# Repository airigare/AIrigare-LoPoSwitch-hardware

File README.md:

LoPoSwitch is designed to switch 12V devices on and off. It can be ruled by Smartphone or Cloud. LoPoSwitch connects to Cloud or Smartphone over WiFi or Bluetooth LE.

## Changelog

### v.0.9.1
- New WiFi Module Adafruit ATWINC1500 WiFi Breakout

### v.0.7
- Connect Digital Pin 1 (Pin3) to Reset Pin. This makes Software Reset possible

### v.0.6
- Switch WiFi Module with Relais
- Redesign PCB Board
- Add 47nP Capacitor

### v.0.5
- Switch WiFi module with Mosfet Transistor            
How to use：

At editor, Click the document icon on the topbar, via "Document" > "Open" > "EasyEDA Source", and select json file, then open it at the editor.

如何使用：

在编辑器顶部工具栏，点击“文档”图标，选择 “文档” > “打开” > “EasyEDA源码”，选择json文件打开即可。

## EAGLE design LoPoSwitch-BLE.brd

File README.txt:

LoPoSwitch is designed to switch 12V devices on and off. It can be ruled by Smartphone or Cloud. LoPoSwitch connects to Cloud or Smartphone over WiFi or Bluetooth LE.

## Changelog
### v.0.6
- Switch WiFi Module with Relais
- Redesign PCB Board
- Add 47nP Capacitor

### v.0.5
- Switch WiFi module with Mosfet Transistor            
How to use：

At editor, Click the document icon on the topbar, via "Document" > "Open" > "EasyEDA Source", and select json file, then open it at the editor.

如何使用：

在编辑器顶部工具栏，点击“文档”图标，选择 “文档” > “打开” > “EasyEDA源码”，选择json文件打开即可。

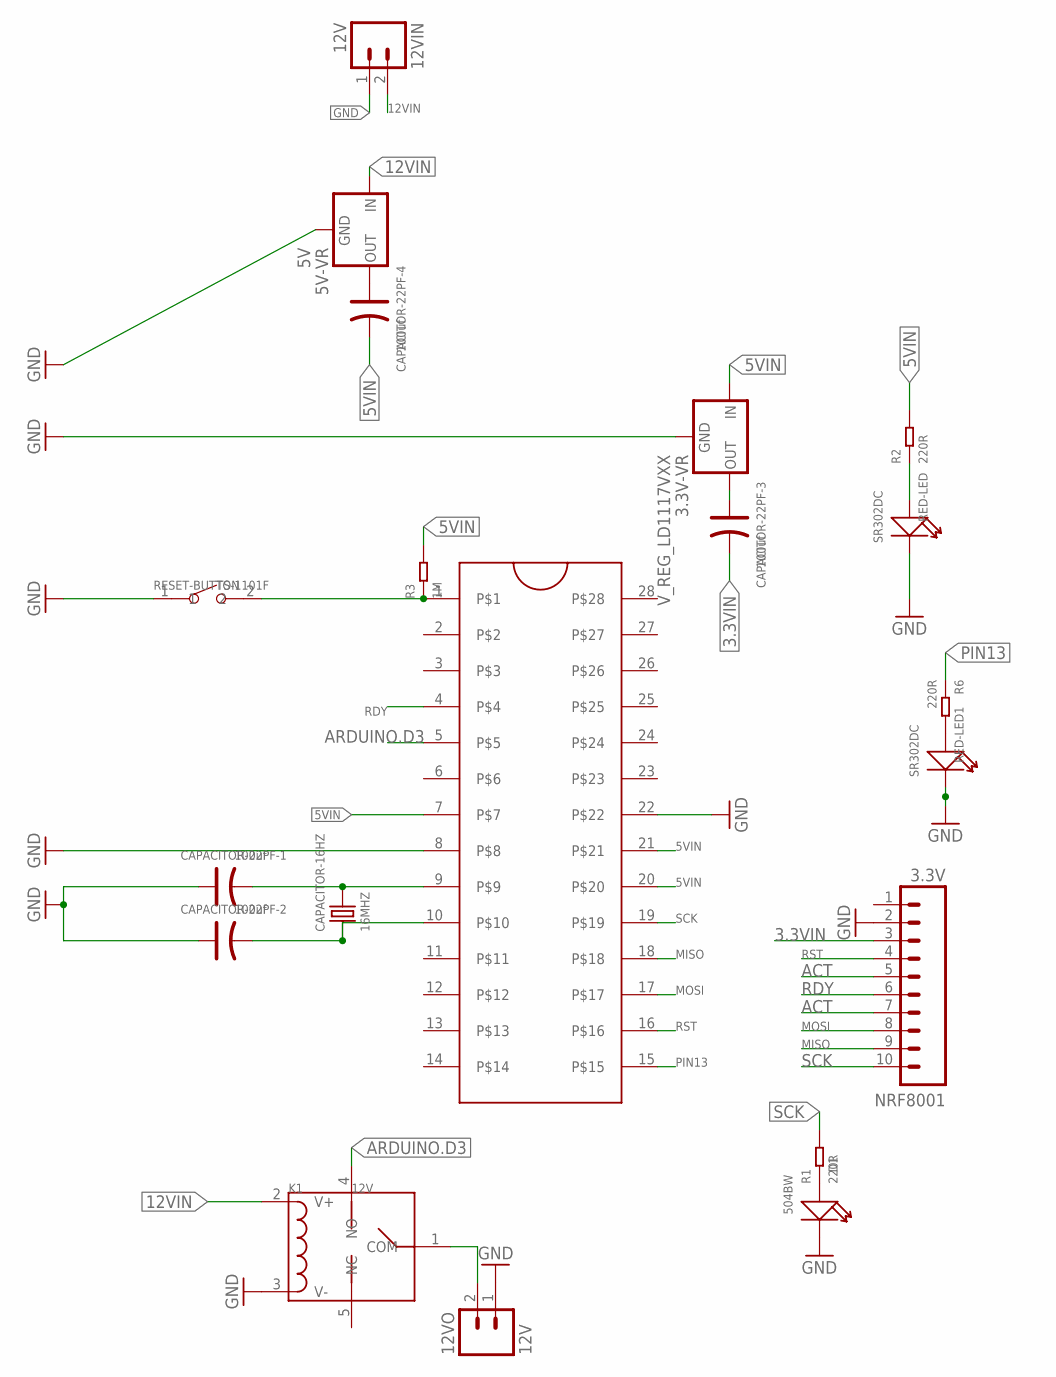
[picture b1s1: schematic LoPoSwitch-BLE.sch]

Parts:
3.3V-VR: V_REG_LD1117VXX; 78XXL
5V-VR: 5V; TO-220-ALT
12VIN, 12VO: 12V; JST-2-PTH
ATMEGA328: ZIFSOCKET-28-3ZIFFSOCKET-28-3; DIL28-3-ZIF_SOCKET
CAPACITOR-16HZ: 16MHZ; HC49US
CAPACITOR-22PF-1, CAPACITOR-22PF-2, CAPACITOR-22PF-3, CAPACITOR-22PF-4: 100uf; PC-D5.3MM
D1: 504BW; LED2-2.54-D5.0MM
K1: 12V; REY5-19.0X15.0X15.0MM
NRF8001: 3.3V; 1X10
R1, R2, R6: 220R; PR-D2.3XL6.5MM
R3: 1M; PR-D2.3XL6.5MM
RED-LED, RED-LED1: SR302DC; LED2-2.54-D3.0MM
RESET-BUTTON: TS-1101F; SW2-5.0-6.0X3.0X4.3MM

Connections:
3.3VIN: CAPACITOR-22PF-3.-, NRF8001.3
5VIN: 3.3V-VR.OUT (IN), ATMEGA328.7, ATMEGA328.20, ATMEGA328.21, CAPACITOR-22PF-4.-, R2.2, R3.2
12VIN: 5V-VR.IN, 12VIN.2, K1.2 (V+)
ACT: NRF8001.5, NRF8001.7
ARDUINO.D3: ATMEGA328.5, K1.4 (NO)
GND: 3.3V-VR.IN (GND), 5V-VR.GND, 12VIN.1, 12VO.1, ATMEGA328.8, ATMEGA328.22, CAPACITOR-22PF-1.+, CAPACITOR-22PF-2.+, D1.-, K1.3 (V-), NRF8001.2, RED-LED.K (-), RED-LED1.K (-), RESET-BUTTON.1
MISO: ATMEGA328.18, NRF8001.9
MOSI: ATMEGA328.17, NRF8001.8
unnamed: 12VO.2, K1.1 (COM)
unnamed: R6.2, RED-LED1.A (+)
unnamed: ATMEGA328.1, R3.1, RESET-BUTTON.2
unnamed: 3.3V-VR.GND (OUT), CAPACITOR-22PF-3.+
unnamed: 5V-VR.OUT, CAPACITOR-22PF-4.+
unnamed: D1.+, R1.1
unnamed: R2.1, RED-LED.A (+)
unnamed: ATMEGA328.9, CAPACITOR-16HZ.2, CAPACITOR-22PF-1.-
unnamed: ATMEGA328.10, CAPACITOR-16HZ.1, CAPACITOR-22PF-2.-
PIN13: ATMEGA328.15, R6.1
RDY: ATMEGA328.4, NRF8001.6
RST: ATMEGA328.16, NRF8001.4
SCK: ATMEGA328.19, NRF8001.10, R1.2

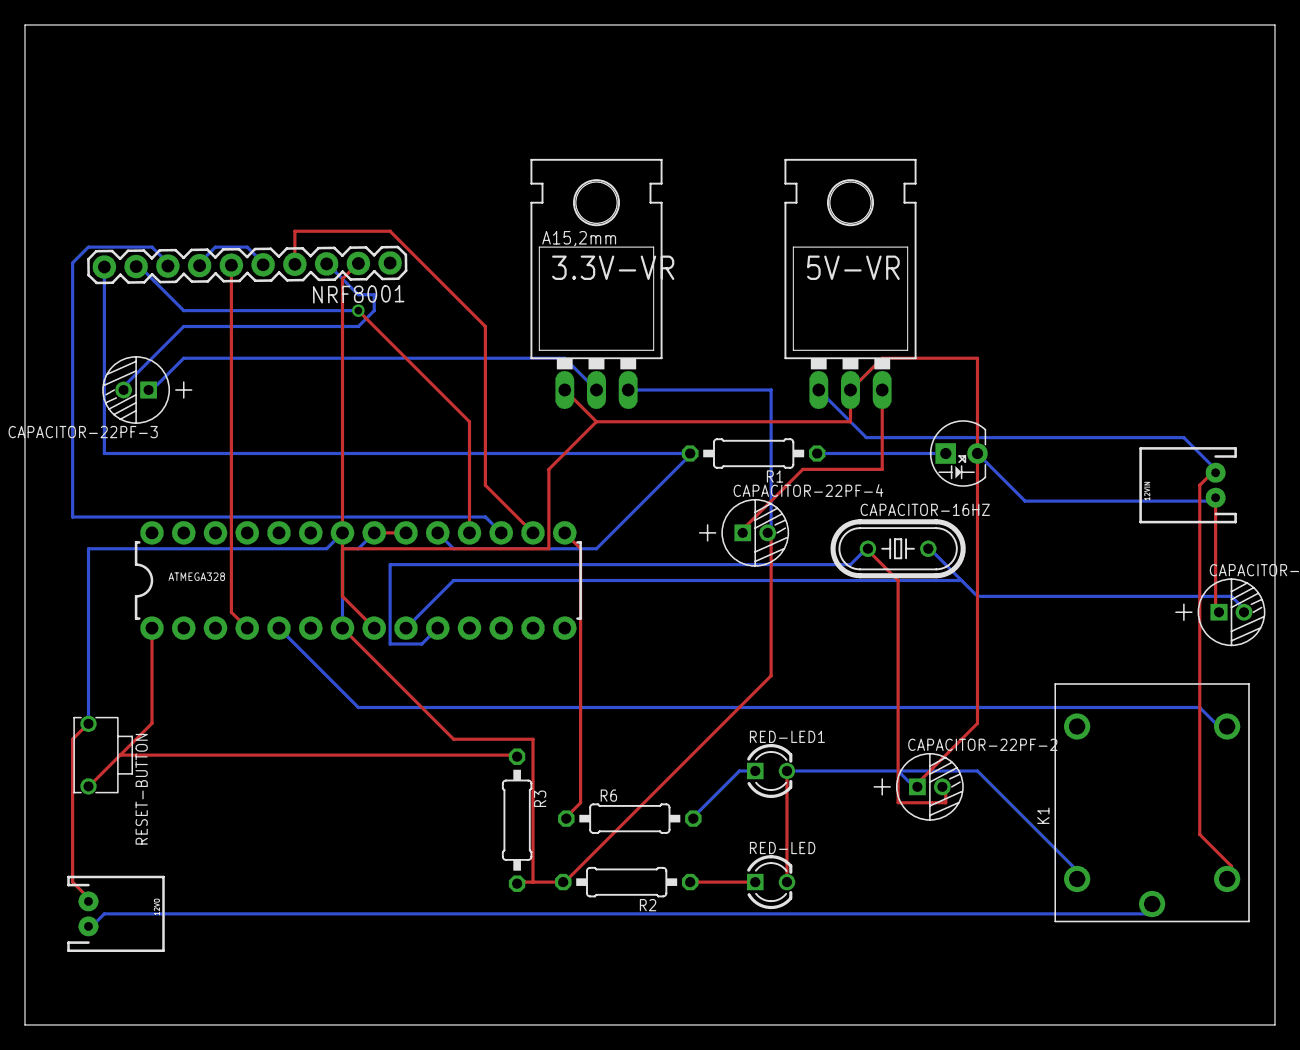
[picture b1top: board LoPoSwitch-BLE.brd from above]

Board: 2 copper layers, 100.0 x 80.0 mm, 20 parts (0 on the bottom side), 21 nets.

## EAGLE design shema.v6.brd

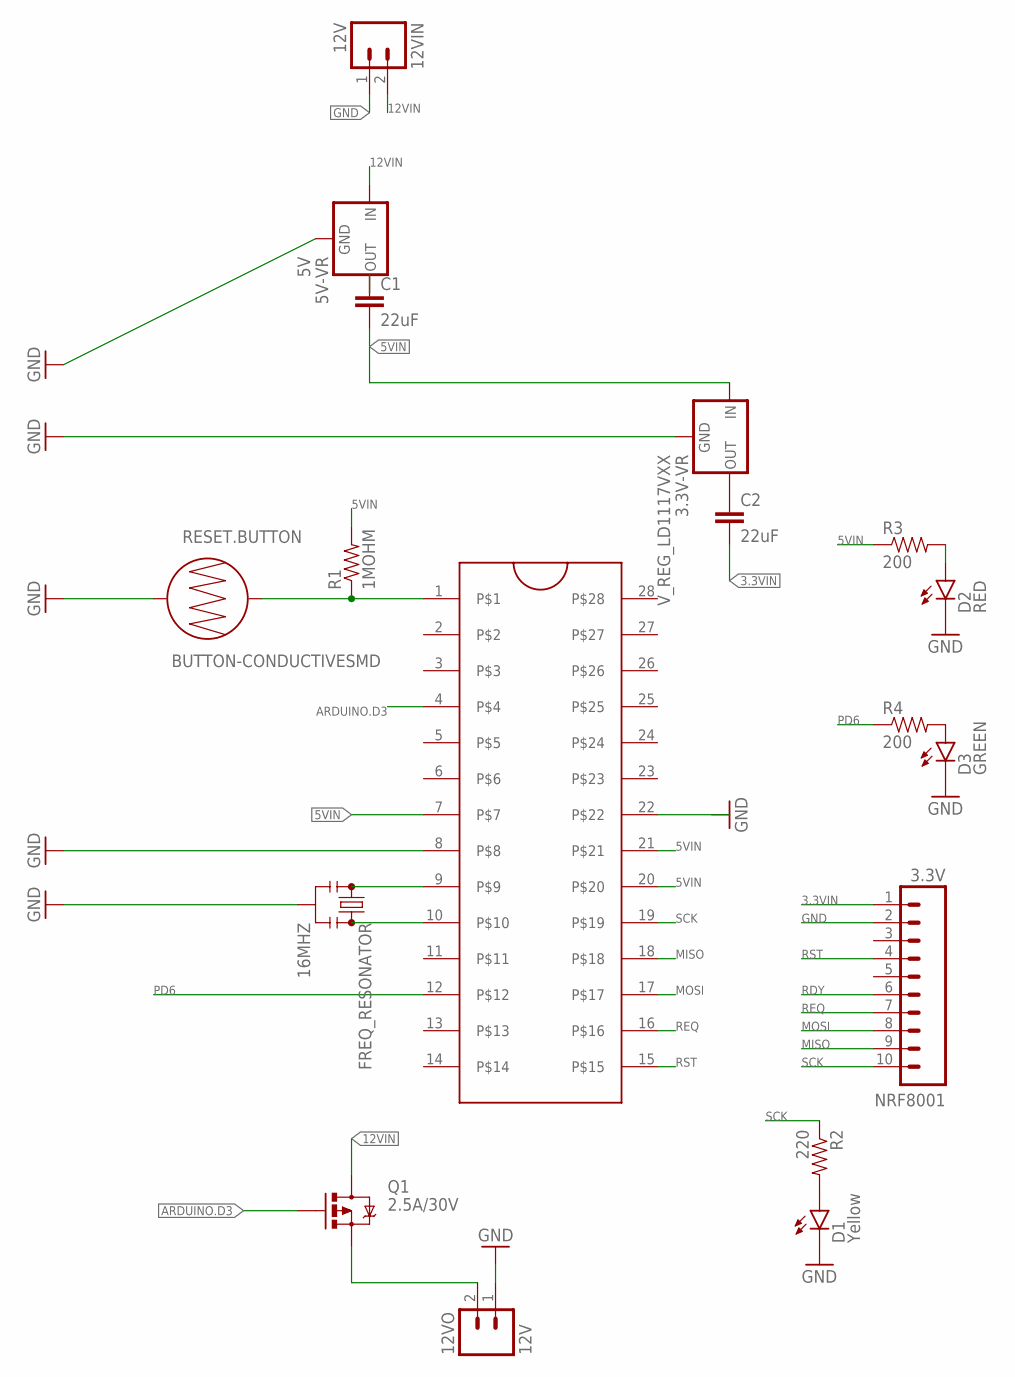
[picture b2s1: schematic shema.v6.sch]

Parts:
3.3V-VR: V_REG_LD1117VXX; 78XXL
5V-VR: 5V; TO-220-ALT
12VIN, 12VO: 12V; JST-2-PTH
ATMEGA328: ZIFSOCKET-28-3ZIFFSOCKET-28-3; DIL28-3-ZIF_SOCKET
C1, C2: 22uF; 1210
D1: Yellow; LED-0603
D2: RED; LED-0603
D3: GREEN; LED-1206
FREQ_RESONATOR: 16MHZ; RESONATOR-SMD
NRF8001: 3.3V; 1X10
Q1: 2.5A/30V; SOT23-3
R1: 1MOHM; 1/6W-RES
R2: 220; AXIAL-0.3EZ
R3, R4: 200; 0603-RES
RESET.BUTTON: BUTTON-CONDUCTIVESMD; BUTTON-CONDUCTIVE

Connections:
3.3VIN: C2.2, NRF8001.1
5VIN: 3.3V-VR.OUT (IN), ATMEGA328.7, ATMEGA328.20, ATMEGA328.21, C1.2, R1.2, R3.1
12VIN: 5V-VR.IN, 12VIN.2, Q1.3 (D)
ARDUINO.D3: ATMEGA328.4, Q1.1 (G)
GND: 3.3V-VR.IN (GND), 5V-VR.GND, 12VIN.1, 12VO.1, ATMEGA328.8, D1.C, D2.C, D3.C, FREQ_RESONATOR.2, NRF8001.2, RESET.BUTTON.1
MISO: ATMEGA328.18, NRF8001.9
MOSI: ATMEGA328.17, NRF8001.8
unnamed: ATMEGA328.9, FREQ_RESONATOR.1
unnamed: ATMEGA328.10, FREQ_RESONATOR.3
unnamed: ATMEGA328.1, R1.1, RESET.BUTTON.2
unnamed: 12VO.2, Q1.2 (S)
unnamed: 5V-VR.OUT, C1.1
unnamed: 3.3V-VR.GND (OUT), C2.1
unnamed: D1.A, R2.P$2 (2)
unnamed: D2.A, R3.2
unnamed: D3.A, R4.2
PD6: ATMEGA328.12, R4.1
RDY: NRF8001.6
REQ: ATMEGA328.16, NRF8001.7
RST: ATMEGA328.15, NRF8001.4
SCK: ATMEGA328.19, NRF8001.10, R2.P$1 (1)

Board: 2 copper layers, 18 parts (0 on the bottom side), 20 nets, no tracks yet.

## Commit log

2016-08-18 Replace MOSFET
2017-09-27 Restyle Board with SeedStudio Elements
2017-09-28 Change Grid to 0.05 inch
2017-09-28 Generate Seed Gerber File
2018-11-16 some versione
2018-11-16 Version 2
2018-11-16 Submit Version 2
2018-11-16 Replace CMD by TO
2018-11-17 V2.1
2019-03-20 v.0.5
    Changelog v.0.5
    - Switch WiFi module with Mosfet Transistor
2019-03-20 v.0.6
    ### v.0.6
    - Switch WiFi Module with Relais
    - Redesign PCB Board
    - Add 47nP Capacitor
2019-03-20 Switch to MarkDown
    Switch Project Description to MarkDown Format
2019-03-21 v.0.7
    Connect Digital Pin to Reset Pin to do Software Reset
2019-05-03 v.0.9.1
    v.0.9.1

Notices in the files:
parts and their libraries:
SparkFun-Connectors: Licensing: Creative Commons ShareAlike 4.0 International - https://creativecommons.org/licenses/by-sa/4.0
